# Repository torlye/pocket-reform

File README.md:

# MNT Pocket Reform: Swapped Ctrl and Hyper keys
This fork modifies `pocket-reform-keyboard-fw` to swap the position of the **Left Ctrl** and **Hyper** keys on the keyboard.

My muscle memory requires me to have the Ctrl key at the bottom left corner of the keyboard!

This fork also adds a few new key combinations:

| Shortcut | Function     |
|----------|--------------|
| HYPER+V  | Volume up    |
| HYPER+C  | Volume down  |
| HYPER+;  | Print screen |

## First-time setup
Run `./install-fw-dependencies.sh`

## Building and flashing
1. cd to `pocket-reform-keyboard-fw/pocket-hid`
2. Run `./build.sh` to build
3. Run the command `sudo sleep 5 && ./flash.sh`
4. Enter your sudo password (if necessary) to begin the sleep
5. Press Hyper+Enter and then x on the keyboard to enter firmware upload mode
6. Wait for flashing to complete and for the controller to reset

---

Original README follows:

---

# MNT Pocket Reform (Research Project)

This repository contains specifications, schematics, PCB and case designs, and firmware source code for the MNT Pocket Reform laptop.

## License

Copyright 2021 MNT Research GmbH.

The following licenses are used in the project, unless specified differently in a particular subfolder:

- Schematics, PCBs: [CERN-OHL-S v2](https://www.ohwr.org/project/cernohl/wikis/uploads/002d0b7d5066e6b3829168730237bddb/cern_ohl_s_v2.txt)
- Other documentation, artwork, photos and drawings that are not trademarks (see below): [CC-BY-SA 4.0](https://creativecommons.org/licenses/by-sa/4.0/legalcode)
- Software, firmware: Various. [GPL 3.0](https://www.gnu.org/licenses/gpl-3.0.en.html) if not specified otherwise in the file/subdirectory.

The "MNT" and "MNT REFORM" logos are trademarks of MNT Research GmbH. You may not use these in derived works. The reason for this is that we cannot be responsible for regulatory issues with derived boards and we cannot support them. If someone sees an MNT brand on a product, it has to be clear that it comes from MNT Research and not from a third party.

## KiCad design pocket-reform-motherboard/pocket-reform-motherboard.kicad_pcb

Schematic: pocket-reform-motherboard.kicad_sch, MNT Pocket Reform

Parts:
C1, C3, C13, C19, C20, C25, C27, C28, C29, C30, C31, C32, C33, C34, C35, C38, C40, C42, C43, C44, C45, C46, C48, C49, C50, C53, C54, C55, C57, C59, C60, C61, C62, C63, C64, C66, C68, C69, C70, C71, C72, C73, C74, C75, C76, C77, C78, C79, C80, C81, C84, C87, C95, C97, C99, C101, C104, C108, C109, C121, C127, C128, C130, C131, C132, C137, C138, C142, C143, C144, C145, C148, C151, C154, C155, C156: 0.1uF; C_0402_1005Metric; LCSC C307331
C2, C7, C12, C39, C47, C51, C56, C58, C65, C98, C105, C107, C112, C115, C129, C133, C136, C141, C152, C153, C157, C158: 10uF; C_0603_1608Metric; LCSC C194427
C4: 22uF; C_Elec_4x5.4; LCSC C3830031
C5: 47uF; CP_Elec_6.3x5.8; LCSC C688950
C6, C14, C15, C16, C17, C18, C116, C117, C118, C119, C120, C134: 22uF; C_0603_1608Metric; LCSC C86295
C8, C11, C82, C113, C114: 470nF; C_0603_1608Metric; LCSC C1623
C9, C10: 4.7uF; C_0603_1608Metric; LCSC C437419
C21, C23: 18pF; C_0402_1005Metric; LCSC C1549
C22, C24: 15pF; C_0402_1005Metric; LCSC C161530
C26, C36, C111, C125, C147: 1uF; C_0402_1005Metric; LCSC C52923
C37: 1nF; C_0402_1005Metric; LCSC C1523
C41, C146: 4.7uF; C_0402_1005Metric; LCSC C23733
C52: 10nF; C_0603_1608Metric; LCSC C1589
C67, C106: 22uF; C_0805_2012Metric; LCSC C45783
C83, C123, C124, C126: 47uF; C_0603_1608Metric; LCSC C140782
C85, C86, C88, C89, C90, C91, C92, C93: 0.22uF; C_0402_1005Metric; LCSC C1525
C94, C100: 10uF; C_0402_1005Metric; LCSC C315248
C96: DNP; C_0402_1005Metric; LCSC C1525; not fitted
C102, C103, C135: 47uF; C_1206_3216Metric; LCSC C94034
C110, C122: 10pF; C_0402_1005Metric; LCSC C32949
D1, D8, D9, D23: LED_RED; LED_0603_1608Metric; LCSC C965799
D2: ESDS314; SOT-23-5; LCSC C1847859
D3: MS2A40LWS; D_SOD-323; LCSC C7380001
D5: PMEG4050EP-FS; D_SOD-128; LCSC C42387310
D10: 19-337/R6GHBHC-A01/2T; LED_19-337_R6GHBHC-A01_2T; LCSC C264519
D12: SD0603S040S0R2; D_0603_1608Metric; LCSC C143772
FB2, FB9, FB10, FB12, FB13, FB14, FB15, FB16: 100@100MHz 3A; L_0603_1608Metric; LCSC C14709
FB5: DNP; L_0603_1608Metric; LCSC C14709; not fitted
GFX1: MountingHole; pocket-reform; LCSC DNP; not fitted
GFX2: MountingHole; pref-motherboard-badge; LCSC DNP; not fitted
H1, H2, H3, H4: MountingHole_Pad; MountingHole_2.2mm_M2_DIN965_Pad; LCSC DNP; not fitted
H5, H7: NGFF-Mount1; WA-SMSI-M2; LCSC C18198647
H8, H9: MountingHole_Pad; WA-SMSI-M2; LCSC C22431115
J1: CHARGER; JST_PH_S9B-PH-SM4-TB_1x09-1MP_P2.00mm_Horizontal; LCSC C278795
J2: DM3AT-SF-PEJM5; LCSC C114218
J3, J14: USB_C_Receptacle; MOLEX_105450-0101; LCSC C134092
J4: 09452812561; LCSC C19193264
J5: SYSCTL; JST_SH_SM04B-SRSS-TB_1x04-1MP_P1.00mm_Horizontal; LCSC C160404
J6: USB_INT1; JST_SH_SM04B-SRSS-TB_1x04-1MP_P1.00mm_Horizontal; LCSC C160404
J7: HDMI_D_1.4; HDMI-SMD_BX-HDMI-2-M19P; LCSC C18077696
J8: SIM_Card; MOLEX_78800-0001; LCSC C127364
J9: Conn_01x20; Hirose_FH12-20S-0.5SH_1x20-1MP_P0.50mm_Horizontal; LCSC C2906119
J10: 1-2199230-6; TE_1-2199230-6; LCSC C4710843
J11: Conn_01x33; Hirose_FH12-33S-0.5SH_1x33-1MP_P0.50mm_Horizontal; LCSC C19077727
J12: 2199230-5; TE_2199230-5; LCSC C4827729
J13: 3-2328724-1; TE_3-2328724-1; LCSC C52722586
J15: CONN_SPK; Molex_PicoBlade_53261-0271_1x02-1MP_P1.25mm_Horizontal; LCSC C177225
J16: SAMTEC_TSM-106-02-X-SH-A; LCSC C6290784
J17: POWSW; JST_SH_SM02B-SRSS-TB_1x02-1MP_P1.00mm_Horizontal; LCSC C160402
J18: CONN_HEAD; JST_SH_SM05B-SRSS-TB_1x05-1MP_P1.00mm_Horizontal; LCSC C136657
J20: QWIIC; JST_SH_SM04B-SRSS-TB_1x04-1MP_P1.00mm_Horizontal; LCSC C160404
L1: 12uH; L_Taiyo-Yuden_NR-30xx; LCSC C167758
L2: 3.3uH; L_1210_3225Metric; LCSC C337905
L3: 3.3uH; L_Coilcraft_XAL6060-XXX; LCSC C3040366
L4: 2.2uH; L_Coilcraft_XAL6060-XXX; LCSC C167218
L5, L6: 15uH; L_Taiyo-Yuden_NR-30xx; LCSC C668450
R1, R16, R29, R34, R35, R36, R45, R58, R60, R61, R63, R71, R110, R165: 1k; R_0402_1005Metric; LCSC C11702
R2: 1M; R_0402_1005Metric; LCSC C26083
R3: 90.9K 1%; R_0402_1005Metric; LCSC C26989
R4, R5, R11, R12, R13, R19, R27, R46, R50, R53, R54, R62, R65, R66, R67, R81, R104, R105, R106, R107, R108, R109, R116, R118, R122, R123, R124, R133, R136, R139, R148, R149, R151, R152, R153, R154, R155, R164, R166, R167, R168, R169, R170: 0; R_0402_1005Metric; LCSC C17168
R6: 470k; R_0402_1005Metric; LCSC C25790
R7: 124k; R_0402_1005Metric; LCSC C36777
R10, R20, R22, R24, R26, R28, R30, R38, R44, R49, R52, R56, R68, R72, R75, R85, R94, R96, R111, R113, R114, R115, R117, R119, R121, R125, R127, R128, R130, R131, R134, R135, R138, R141, R142, R143, R144, R145, R156, R159, R160, R162, R163: 10k; R_0402_1005Metric; LCSC C25744
R14: 8.25k; R_0402_1005Metric; LCSC C95598
R15: 33k; R_0402_1005Metric; LCSC C25779
R17, R51, R69, R70, R87, R91, R112, R150, R157: 100k; R_0402_1005Metric; LCSC C25741
R18: 24.9k; R_0402_1005Metric; LCSC C25874
R21, R74, R78, R88: DNP; R_0402_1005Metric; LCSC DNP; not fitted
R23: 9.53K 1%; R_0402_1005Metric; LCSC C96273
R25, R42, R43, R57, R59, R95, R101, R120, R161: 4.7k; R_0402_1005Metric; LCSC C25900
R31: 0; R_0603_1608Metric; LCSC C21189
R32, R33, R64, R89, R93, R132, R137, R158: 2.2k; R_0402_1005Metric; LCSC C25879
R37, R39, R40, R41: 75 1%; R_0402_1005Metric; LCSC C25133
R47, R48: 27.4; R_0402_1005Metric; LCSC C31439
R55, R76, R77, R79, R80, R82, R86: 33; R_0402_1005Metric; LCSC C25105
R73, R97, R98, R99, R100: 47k; R_0402_1005Metric; LCSC C25792
R83, R84: 22k; R_0402_1005Metric; LCSC C25768
R90: 27k; R_0402_1005Metric; LCSC C25771
R92, R126: 4.99k; R_0402_1005Metric; LCSC C25903
R102: 43.2k; R_0402_1005Metric; LCSC C25894
R103: 0; R_0402_1005Metric; LCSC C17168; not fitted
R129: 6.8k; R_0402_1005Metric; LCSC C25917
R198, R199: 49.9; R_0402_1005Metric; LCSC C25120
SW1: SW_DIP_x01; SW_DIP_SPSTx01_Slide_Copal_CHS-01A_W5.08mm_P1.27mm_JPin; LCSC C3312106
SW2, SW3: RESET; SW_Push_1P1T_NO_CK_KMR2; LCSC C318893
TP1, TP2, TP3, TP4, TP5, TP6, TP10, TP11, TP12, TP13, TP14, TP15, TP16, TP17, TP18, TP19, TP20, TP21: TestPoint; TestPoint_Pad_D1.0mm; not fitted
TP7: UUART_SUSPEND; TestPoint_Pad_D1.0mm; not fitted
TP8: UUART_WAKEUP; TestPoint_Pad_D1.0mm; not fitted
TP9: UUART_nPOWER; TestPoint_Pad_D1.0mm; not fitted
TR1: TG111-MSC13LF; Transformer_Ethernet_HALO_TG111-MSC13; LCSC C501477
U1: reform2-som-connector; TE_1473149-4; LCSC C590722
U2, U30, U31, U37: TS3USB30EDGSR; VSSOP-10_3x3mm_P0.5mm; LCSC C131998
U3: LM2830XQMFE/NOPB; SOT-23-5; LCSC C2072452
U4: TLV75718PDBV; SOT-23-5; LCSC C507270
U5: LM73100RPWR; IC_LM73100RPWR; PARTREV 08/2019; LCSC C3210761
U6, U28: LM62460; CONV_LM61495QRPHRQ1; LCSC C3198091
U7: 74LVC1G34; SOT-353_SC-70-5; LCSC C353880
U8: RP2040; RP2040-QFN-56; LCSC C2040
U9: TPS7A0533PDBZ; SOT-23; LCSC C2877921
U10: W25Q32JVSS; SOIC-8_5.3x5.3mm_P1.27mm; LCSC C179173
U11: PCF8523T; SOIC-8_3.9x4.9mm_P1.27mm; LCSC C2651516
U12, U29, U32, U36, U40, U41: AP22615AWU-7; SOT-23-6; LCSC C2680357
U13, U24: TXS0108EPW; TSSOP-20_4.4x6.5mm_P0.65mm; LCSC C17206
U14: SN74AVC1T45; SOT-23-6; LCSC C131978
U15, U16, U19, U20, U21, U22: TPD4E02B04DQA; USON-10_2.5x1.0mm_P0.5mm; LCSC C2841426
U17: TPD12S521; TSSOP50P640X120-38N; LCSC C126920
U18: TLV320AIC3100; VQFN-32-1EP_5x5mm_P0.5mm_EP3.5x3.5mm; LCSC C478458
U23: FUSB302BMPX; WQFN-14-1EP_2.5x2.5mm_P0.5mm_EP1.45x1.45mm; LCSC C132291
U25: TUSB8041; QFN-64-1EP_9x9mm_P0.5mm_EP6x6mm_ThermalVias; LCSC C544686
U27: TVS2200DRV; WSON-6-1EP_2x2mm_P0.65mm_EP1x1.6mm; LCSC C523793
U33: AT24CS02-STUM; SOT-23-5; LCSC C2060969
U34: PCA9536DP; TSSOP-8_3x3mm_P0.65mm; LCSC C14674
U35: TMUXHS4446RETR; IC_TMUXHS4446RETR; PARTREV FEBRUARY 2024; LCSC C35471229
U38: CY7C65215-32LTXI; QFN-32-1EP_5x5mm_P0.5mm_EP3.45x3.45mm; LCSC C22451897
U39: PCA9557PW; TSSOP-16_4.4x5mm_P0.65mm; LCSC C141380
U42: TPS560430X3FDBVR; SOT-23-6; LCSC C2071721
Y1: 24MHz; Crystal_SMD_Abracon_ABM8G-4Pin_3.2x2.5mm; LCSC C91744
Y2: 12MHz 12pF; Crystal_SMD_3225-4Pin_3.2x2.5mm; LCSC C20625731
Y3: 32.768 kHz; Crystal_SMD_3215-2Pin_3.2x1.5mm; LCSC C48615

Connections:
3V3_ENABLE_L: R71.2, R121.2, U32.4 (EN), U39.9 (IO2)
5V_ENABLE_L: R63.2, U39.7 (IO1)
+1V1: C134.1, L2.2, R14.1, R50.1, TP15.1 (1_1)
+1V8: C10.1, C20.1, C41.1, FB12.1, J13.1, R53.1, R81.2, TP14.1 (1_1), U4.5 (OUT), U7.5 (VCC)
+3V3: C58.1, C77.1, C116.1, C117.1, C118.1, C119.1, C120.1, C133.1, C141.1, FB5.2, FB13.2, L4.2, R4.2, R24.1, R26.1, R29.1, R30.1, R34.1, R42.2, R43.2, R54.2, R85.1, R87.1, R90.1, R91.1, R92.1, R97.2, R98.2, R99.2, R100.2, R112.2, R128.2, R136.2, R154.2, R156.2, R157.1, R160.2, R164.2, TP13.1 (1_1), U28.5 (BIAS), U29.6 (IN), U36.6 (IN), U40.6 (IN)
+5V: C14.1, C15.1, C16.1, C17.1, C18.1, C39.1, C47.1, C73.2, C108.1, C136.1, D12.2 (A), FB2.1, L3.2, R3.1, R11.1, R17.1, R51.2, R62.1, R68.2, R103.2, R126.1, R142.2, TP12.1 (1_1), U1.1 (5V), U1.2 (5V), U1.3 (5V), U1.4 (5V), U1.5 (5V), U1.6 (5V), U6.5 (BIAS), U9.3 (VI), U12.6 (IN), U17.1 (5V_SUPPLY), U41.6 (IN)
/3V3_1V8: C9.1, R4.1, U4.1 (IN), U4.3 (EN)
/AUD_3V3: C50.1, C51.1, C97.1, C107.1, FB5.1, J18.1, U9.2 (VO), U18.17 (AVDD), U18.28 (HPVDD)
/DP0_N: J9.8, R148.1
/DP0_P: J9.7, R149.1
/DP1_N: J9.5, R151.1
/DP1_P: J9.4, R152.1
/DP2_N: J9.2, R169.1
/DP2_P: J9.1, R170.1
/DP3_N: J9.11, R167.1
/DP3_P: J9.10, R168.1
/DP_AUX_N: C138.2, J9.15
/DP_AUX_P: C137.2, J9.16
/M2_SMB_ALERTn: J10.44
/M2_SMB_CLK: J10.40
/M2_SMB_DATA: J10.42
/MODEM_3V3: C52.1, C53.1, C54.1, C55.1, C83.1, C123.1, J12.2, J12.4, J12.70, J12.72, J12.74, R1.1, R164.1, R166.2
/M_ANTCTL0: J12.59
/M_ANTCTL1: J12.61
/M_ANTCTL2: J12.58
/M_ANTCTL3: J12.56
/M_COEX1: J12.64
/M_COEX2: J12.62
/M_CONFIG_0: J12.21
/M_CONFIG_1: J12.69
/M_CONFIG_2: J12.75
/M_CONFIG_3: J12.1
/M_I2C_SCL: J12.38
/M_I2C_SDA: J12.68
/M_I2S_MCLK(IO): J12.60
/M_LAA_TX_EN: J12.63
/M_SIM1_DET: J12.66
/M_SIM2_CLK: J12.44
/M_SIM2_DATA: J12.42
/M_SIM2_DET: J12.40
/M_SIM2_PWR: J12.48
/M_SIM2_RESET: J12.46
/M_VIO_1V8: J12.65
/PCIE_3V3: C59.1, C60.1, C61.1, C124.1, C126.1, J10.2, J10.4, J10.12, J10.14, J10.16, J10.18, J10.70, J10.72, J10.74, R110.1, U29.1 (OUT)
/RRUD+: R47.1, U8.47 (USB_DP)
/RRUD-: R48.1, U8.46 (USB_DM)
/RUD+: R47.2, U2.3 (D2+), U30.4 (D+)
/RUD-: R48.2, U2.7 (D2-), U30.6 (D-)
/SYSLED_B: R61.1, U8.18 (GPIO15)
/SYSLED_G: R58.1, U8.28 (GPIO17)
/SYSLED_R: R60.1, U8.27 (GPIO16)
/USB1_C_RXN: C128.2, U25.56 (USB_SSTXM_UP)
/USB1_C_RXP: C127.2, U25.55 (USB_SSTXP_UP)
/USBH_1A_AC_TXN: C85.1, J3.A3 (TX1-), U20.4 (IO3), U20.7 (IO3)
/USBH_1A_AC_TXP: C88.1, J3.A2 (TX1+), U20.5 (IO4), U20.6 (IO4)
/USBH_1B_AC_TXN: C86.1, J3.B3 (TX2-), U22.1 (IO1), U22.10 (IO1)
/USBH_1B_AC_TXP: C89.1, J3.B2 (TX2+), U22.2 (IO2), U22.9 (IO2)
/USBM1_AC_RXN: J14.B10 (RX1-), U19.1 (IO1), U19.10 (IO1), U35.25 (CRX1+)
/USBM1_AC_RXP: J14.B11 (RX1+), U19.2 (IO2), U19.9 (IO2), U35.24 (CRX1-)
/USBM1_AC_TXN: C90.2, J14.A3 (TX1-), U19.4 (IO3), U19.7 (IO3)
/USBM1_AC_TXP: C92.2, J14.A2 (TX1+), U19.5 (IO4), U19.6 (IO4)
/USBM1_TXN: C92.1, U35.27 (CTX1-)
/USBM1_TXP: C90.1, U35.28 (CTX1+)
/USBM2_AC_RXN: J14.A10 (RX2-), U21.1 (IO1), U21.10 (IO1), U35.34 (CRX2+)
/USBM2_AC_RXP: J14.A11 (RX2+), U21.2 (IO2), U21.9 (IO2), U35.33 (CRX2-)
/USBM2_AC_TXN: C91.2, J14.B3 (TX2-), U21.4 (IO3), U21.7 (IO3)
/USBM2_AC_TXP: C93.2, J14.B2 (TX2+), U21.5 (IO4), U21.6 (IO4)
/USBM2_TXN: C93.1, U35.30 (CTX2-)
/USBM2_TXP: C91.1, U35.31 (CTX2+)
/USBM_SBU1: J14.A8 (SBU1), U35.22 (SBU1)
/USBM_SBU2: J14.B8 (SBU2), U35.21 (SBU2)
/USB_UART_3V3: C146.1, R134.1, R135.1, R136.1, U38.1 (VDDD), U38.19 (VBUS), U38.23 (VDDD)
/VCONN: R166.1, U23.12 (VCONN), U23.13 (VCONN)
/VIN_FOR_3V3: C112.1, C113.1, C114.1, C115.1, U28.2 (VIN2), U28.14 (VIN1), U32.1 (OUT)
/XUD+: U2.4 (D+), U31.3 (D2+)
/XUD-: U2.6 (D-), U31.7 (D2-)
/~M_LED1: D1.1 (K), J12.10
/~M_W_DISABLE1: J12.8, R65.1
/~M_W_DISABLE2: J12.26, R66.1
/~PCIE2_CLKREQ: J12.52
/~PCIE2_WAKE: J12.54
CHG_VCC: C4.1, J1.1, J1.2, R6.1, U5.5 (IN)
DAC_BCLK: R76.1, U1.170 (SAI2_TXC)
DAC_DIN: R79.1, U1.166 (SAI2_RXD)
DAC_DOUT: R77.1, U1.178 (SAI2_TXD)
DAC_MCLK: R82.2, U1.176 (SAI2_MCLK)
DAC_SCL: R42.1, U1.101 (I2C3_SCL), U11.6 (SCL), U18.10 (SCL)
DAC_SDA: R43.1, U1.103 (I2C3_SDA), U11.5 (SDA), U18.9 (SDA)
DAC_TXFS: R80.1, U1.172 (SAI2_TXFS)
DISP_1BL_2EN: J13.26, U1.105 (GPIO1_IO10)
DISP_1EN_2BL: J13.2, R46.2, R138.1, R139.2
DISP_2_PWM: R139.1, U8.9 (GPIO7)
DISP_BACKLIGHT_3V3: C105.1, J13.5, J13.6, J13.28, J13.29, J13.30, J13.31, R138.2, U36.1 (OUT)
DISP_BL_PWR_EN_L: R130.2, U36.4 (EN), U39.12 (IO5)
DP_HPD: J9.17, R165.2
DSI_CLK_N: J11.19, J13.17
DSI_CLK_P: J11.20, J13.16
DSI_D0_N: J11.25, J13.20
DSI_D0_P: J11.26, J13.19
DSI_D1_N: J11.22, J13.14
DSI_D1_P: J11.23, J13.13
DSI_D2_N: J11.16, J13.11
DSI_D2_P: J11.17, J13.10
DSI_D3_N: J11.13, J13.23
DSI_D3_P: J11.14, J13.22
ETH0_A+: TR1.2 (TD1+), U1.29 (TRX0_P)
ETH0_A-: TR1.3 (TD1-), U1.27 (TRX0_N)
ETH0_B+: TR1.5 (TD2+), U1.23 (TRX1_P)
ETH0_B-: TR1.6 (TD2-), U1.21 (TRX1_N)
ETH0_C+: TR1.8 (TD3+), U1.17 (TRX2_P)
ETH0_C-: TR1.9 (TD3-), U1.15 (TRX2_N)
ETH0_D+: TR1.11 (TD4+), U1.11 (TRX3_P)
ETH0_D-: TR1.12 (TD4-), U1.9 (TRX3_N)
ETH0_DA+: J4.1, TR1.23 (MTX1+)
ETH0_DA-: J4.2, TR1.22 (MTX1-)
ETH0_DB+: J4.6, TR1.20 (MTX2+)
ETH0_DB-: J4.7, TR1.19 (MTX2-)
ETH0_DC+: J4.4, TR1.17 (MTX3+)
ETH0_DC-: J4.5, TR1.16 (MTX3-)
ETH0_DD+: J4.9, TR1.14 (MX4+)
ETH0_DD-: J4.10, TR1.13 (MX4-)
ETH0_LED_LINK1: D9.1 (K), U1.83 (JTAG_TDO)
ETH0_LED_RX: D8.1 (K), U1.79 (JTAG_MOD)
GND: C1.2, C2.2, C3.2, C4.2, C5.2, C6.2, C7.2, C8.2, C9.2, C10.2, C11.2, C12.2, C13.1, C14.2, C15.2, C16.2, C17.2, C18.2, C20.2, C21.2, C22.2, C23.2, C24.2, C25.2, C26.2, C27.2, C28.2, C29.2, C30.2, C31.2, C32.2, C33.2, C34.2, C35.2, C36.2, C37.2, C38.2, C39.2, C40.2, C41.2, C42.2, C43.2, C44.2, C45.2, C46.1, C47.2, C48.2, C49.2, C52.2, C53.2, C54.2, C55.2, C56.2, C58.2, C59.2, C60.2, C61.2, C62.2, C63.2, C64.2, C65.2, C66.2, C68.2, C69.2, C70.2, C71.2, C72.1, C73.1, C74.2, C75.2, C77.2, C79.2, C80.2, C81.2, C83.2, C84.2, C87.2, C94.2, C95.1, C98.2, C100.2, C101.2, C105.2, C108.2, C111.1, C112.2, C113.2, C114.2, C115.2, C116.2, C117.2, C118.2, C119.2, C120.2, C123.2, C124.2, C125.1, C126.2, C129.2, C130.2, C131.2, C132.1, C133.2, C134.2, C135.2, C136.2, C141.2, C142.2, C143.2, C144.2, C145.2, C146.2, C147.2, C148.2, C151.2, C152.2, C153.2, C154.1, C155.1, C156.1, C157.2, C158.2, D2.2 (A), D3.2 (A), D10.1 (RK), D10.2 (GK), D10.3 (BK), FB14.1, FB15.1, FB16.1, H1.1 (1_1), H2.1 (1_1), H3.1 (1_1), H4.1 (1_1), H5.1 (1_1), H7.1 (1_1), H8.1 (1_1), H9.1 (1_1), J1.8, J1.9, J2.6 (VSS), J2.P1 (SHIELD), J2.P2 (SHIELD), J2.P3 (SHIELD), J2.P4 (SHIELD), J2.SWA (DET_A), J3.A1 (GND), J3.A12 (GND), J3.B1 (GND), J3.B12 (GND), J3.S1 (SHIELD), J4.3, J4.8, J4.SH, J5.4, J6.4, J7.4 (D2S), J7.7 (D1S), J7.10 (D0S), J7.13 (CKS), J7.16 (GND), J7.20 (SH), J8.5 (GND), J8.P1 (SHIELD), J8.P2 (SHIELD), J8.P3 (SHIELD), J8.P4 (SHIELD), J9.3, J9.6, J9.9, J9.12, J9.13, J10.1, J10.3, J10.9, J10.15, J10.21, J10.27, J10.33, J10.39, J10.45, J10.51, J10.57, J10.71, J10.73, J10.75, J10.S1 (SHIELD), J10.S2 (SHIELD), J11.1, J11.2, J11.12, J11.15, J11.18, J11.21, J11.24, J11.27, J11.30, J12.3, J12.5, J12.11, J12.27, J12.33, J12.39, J12.45, J12.51, J12.57, J12.71, J12.73, J12.SH1 (SHIELD), J12.SH2 (SHIELD), J13.3, J13.4, J13.9, J13.12, J13.15, J13.18, J13.21, J13.24, J13.27, J13.S1 (Pin_32), J13.S2 (Pin_33), J14.A1 (GND), J14.A12 (GND), J14.B1 (GND), J14.B12 (GND), J14.S1 (SHIELD), J16.1, J16.4, J17.1, J20.1, R10.2, R15.2, R16.2, R18.2, R20.2, R22.2, R23.1, R32.2, R33.2, R49.1, R69.2, R73.2, R94.2, R95.1, R96.2, R101.1, R102.2, R104.2, R105.2, R106.2, R107.2, R108.2, R109.2, R115.2, R120.2, R121.1, R125.2, R129.2, R130.1, R141.2, R143.1, R144.1, R145.1, R150.2, R158.2, R159.1, R161.2, R162.1, R198.1, R199.1, SW1.2, SW2.2 (B), SW3.2 (B), TP3.1 (1_1), TP19.1 (1_1), U1.7 (GND), U1.13 (GND), U1.19 (GND), U1.25 (GND), U1.31 (GND), U1.41 (GND), U1.44 (GND), U1.47 (GND), U1.50 (GND), U1.53 (GND), U1.56 (GND), U1.59 (GND), U1.62 (GND), U1.65 (GND), U1.68 (GND), U1.71 (GND), U1.74 (GND), U1.80 (GND), U1.94 (GND), U1.95 (GND), U1.98 (GND), U1.99 (GND), U1.104 (GND), U1.110 (GND), U1.111 (GND), U1.116 (GND), U1.117 (GND), U1.123 (GND), U1.129 (GND), U1.161 (GND), U1.167 (GND), U1.173 (GND), U1.179 (GND), U1.185 (GND), U1.191 (GND), U2.5 (GND), U3.2 (GND), U4.2 (GND), U5.8 (GND), U6.1 (PGND2), U6.8 (AGND), U6.12 (SYNC/MODE), U6.15 (PGND1), U7.3 (GND), U8.19 (TESTEN), U8.57 (GND), U9.1 (GND), U10.4 (GND), U11.4 (VSS), U12.2 (GND), U13.11 (GND), U14.2 (GND), U15.3 (G), U15.8 (G), U16.3 (G), U16.8 (G), U17.3 (GND), U17.5 (TMDS_GND), U17.8 (TMDS_GND), U17.11 (TMDS_GND), U17.14 (TMDS_GND), U17.25 (TMDS_GND), U17.28 (TMDS_GND), U17.31 (TMDS_GND), U17.34 (TMDS_GND), U17.36 (GND), U18.1 (IOVSS), U18.18 (DVSS), U19.3 (G), U19.8 (G), U20.3 (G), U20.8 (G), U21.3 (G), U21.8 (G), U22.3 (G), U22.8 (G), U23.8 (GND), U23.9 (GND), U23.15 (GND), U24.11 (GND), U25.65 (VSS), U27.1 (GND), U27.2 (GND), U27.3 (GND), U27.7 (GND), U28.1 (PGND2), U28.8 (AGND), U28.12 (SYNC/MODE), U28.15 (PGND1), U29.2 (GND), U30.5 (GND), U31.5 (GND), U32.2 (GND), U33.2 (GND), U33.5 (WP), U34.4 (VSS), U35.15 (GND), U35.18 (GND), U35.37 (GND), U35.41 (GND), U36.2 (GND), U37.5 (GND), U38.4 (VSSD), U38.17 (VSSD), U38.20 (VSSD), U38.24 (VSSA), U39.4 (A1), U39.5 (A2), U39.8 (VSS), U40.2 (GND), U41.2 (GND), U42.2 (GND), Y1.2, Y1.4, Y2.2, Y2.4
GNDA: C50.2, C51.2, C57.2, C67.2, C76.2, C78.2, C96.1, C97.2, C99.2, C106.2, C107.2, FB14.2, FB15.2, FB16.2, J18.5, U18.16 (AVSS), U18.20 (SPKVSS), U18.25 (SPKVSS), U18.29 (HPVSS), U18.33 (EP)
HDMI_AUXN: U1.189 (HDMI_AUX_N)
HDMI_AUXP: U1.187 (HDMI_AUX_P)
HDMI_CEC: R100.1, U1.197 (HDMI_CEC), U17.16 (CE_REMOTE_IN)
HDMI_CLKN: J7.14 (CK-), U1.163 (HDMI_CLK_N), U17.15 (TMDS_CK-), U17.24 (TMDS_CK-)
HDMI_CLKP: J7.12 (CK+), U1.165 (HDMI_CLK_P), U17.13 (TMDS_CK+), U17.26 (TMDS_CK+)
HDMI_HPD: R97.1, U1.199 (HDMI_HPD), U17.19 (HOTPLUG_DET_IN)
HDMI_SCL: R98.1, U1.195 (HDMI_DDC_SCL), U17.17 (DDC_CLK_IN)
HDMI_SDA: R99.1, U1.193 (HDMI_DDC_SDA), U17.18 (DDC_DAT_IN)
HDMI_TX0N: J7.11 (D0-), U1.169 (HDMI_TX0_N), U17.12 (TMDS_D0-), U17.27 (TMDS_D0-)
HDMI_TX0P: J7.9 (D0+), U1.171 (HDMI_TX0_P), U17.10 (TMDS_D0+), U17.29 (TMDS_D0+)
HDMI_TX1N: J7.8 (D1-), U1.175 (HDMI_TX1_N), U17.9 (TMDS_D1-), U17.30 (TMDS_D1-)
HDMI_TX1P: J7.6 (D1+), U1.177 (HDMI_TX1_P), U17.7 (TMDS_D1+), U17.32 (TMDS_D1+)
HDMI_TX2N: J7.5 (D2-), U1.181 (HDMI_TX2_N), U17.6 (TMDS_D2-), U17.33 (TMDS_D2-)
HDMI_TX2P: J7.3 (D2+), U1.183 (HDMI_TX2_P), U17.4 (TMDS_D2+), U17.35 (TMDS_D2+)
HEAD_HPL: C103.2, J18.3
HEAD_HPR: C102.2, J18.4
HEAD_MIC: C96.2, C104.2, J18.2, R64.1, U18.11 (VOL/MICDET)
HUB_PWR_EN_L: R162.2, U39.10 (IO3), U40.4 (EN)
IMX_RESETn: R30.2, U1.87 (EXT_RESET_N)
IMX_RTC_IRQ: R67.1, U1.141 (RTC_IRQ)
IMX_UART1_RX: J16.5, R26.2, R134.2, U1.126 (UART1_RXD), U38.30 (SCB0_4/GPIO_5)
IMX_UART1_TX: J16.6, U1.128 (UART1_TXD), U38.2 (SCB0_0/GPIO_8)
IMX_UART2_RX: J16.2, R24.2, R135.2, U1.122 (UART2_RXD), U38.6 (SCB1_1/GPIO_11)
IMX_UART2_TX: J16.3, U1.124 (UART2_TXD), U38.5 (SCB1_0/GPIO_10)
IMX_WAKE: U1.145 (GPIO1_IO3), U8.30 (GPIO19)
KICKSTART: R44.2, R45.2, SW3.1 (A)
LPC_MISO: TP11.1 (1_1), U1.93 (ECSPI2_MISO), U8.14 (GPIO11)
LPC_MOSI: TP5.1 (1_1), U1.91 (ECSPI2_MOSI), U8.11 (GPIO8)
LPC_SCK: TP10.1 (1_1), U1.97 (ECSPI2_SCLK), U8.13 (GPIO10)
LPC_SS0: TP6.1 (1_1), U1.89 (ECSPI2_SS0), U8.12 (GPIO9)
MODEM_PWROFFn: J12.6, U8.29 (GPIO18)
MODEM_RESET: J12.67, U24.6 (A5)
MODEM_RESET_3V3: U8.31 (GPIO20), U24.15 (B5)
unnamed: C24.1, R35.1, Y2.3
unnamed: C37.1, R37.2, R39.2, R40.2, R41.2
unnamed: C57.1, C67.1, C99.1, C106.1, FB2.2, U18.21 (SPKVDD), U18.24 (SPKVDD)
unnamed: C110.2, R126.2
unnamed: C122.2, R92.2
unnamed: D1.2 (A), R1.2
unnamed: D3.1 (K), L2.1, U3.1 (SW)
unnamed: D8.2 (A), R29.2
unnamed: D9.2 (A), R34.2
unnamed: D10.4 (BA), R61.2
unnamed: D10.5 (GA), R60.2
unnamed: D10.6 (RA), R58.2
unnamed: D12.1 (K), R89.1, R93.1
unnamed: D23.2 (A), R110.2
unnamed: D23.1 (K), J10.10
unnamed: FB9.1, U18.22 (SPKP), U18.26 (SPKP)
unnamed: FB9.2, L5.1
unnamed: FB10.1, U18.19 (SPKM), U18.23 (SPKM)
unnamed: FB10.2, L6.1
unnamed: J2.5 (CLK), U14.4 (B)
unnamed: C63.1, C64.1, C65.1, C66.1, J2.4 (VDD), R154.1, U13.19 (VCCB), U14.6 (VCCB)
unnamed: J3.A5 (CC1), R83.1, U16.1 (IO1), U16.10 (IO1)
unnamed: J3.B5 (CC2), R84.1, U16.2 (IO2), U16.9 (IO2)
unnamed: J6.1, R62.2
unnamed: C87.1, J7.19 (+5V), U17.38 (5V_OUT)
unnamed: J7.15 (CEC), R90.2, U17.23 (CE_REMOTE_OUT)
unnamed: J7.1 (HPD/HEAC-), R96.1, U17.20 (HOTPLUG_DET_OUT)
unnamed: J7.17 (SCL), R89.2, U17.22 (DDC_CLK_OUT)
unnamed: J7.18 (SDA), R93.2, U17.21 (DDC_DAT_OUT)
unnamed: J9.18, J9.19, J9.20, R103.1
unnamed: J10.11, R107.1
unnamed: J10.13, R104.1
unnamed: J10.23, R108.1
unnamed: J10.25, R105.1
unnamed: J10.35, R109.1
unnamed: J10.37, R106.1
unnamed: J14.A5 (CC1), TP20.1 (1_1), U15.1 (IO1), U15.10 (IO1), U23.10 (CC1), U23.11 (CC1)
unnamed: J14.B5 (CC2), TP21.1 (1_1), U15.2 (IO2), U15.9 (IO2), U23.1 (CC2), U23.14 (CC2)
unnamed: C76.1, C82.1, J15.1, L5.2
unnamed: C78.1, C82.2, J15.2, L6.2
unnamed: R40.1, TR1.21 (MCT2)
unnamed: R39.1, TR1.18 (MCT3)
unnamed: R37.1, TR1.15 (MCT4)
unnamed: R41.1, TR1.24 (MTC1)
unnamed: C42.1, TR1.1 (TCT1)
unnamed: C43.1, TR1.4 (TCT2)
unnamed: C44.1, TR1.7 (TCT3)
unnamed: C45.1, TR1.10 (TCT4)
unnamed: R116.1, U1.139 (FAST_BOOT)
unnamed: R74.2, U1.180 (SAI3_MCLK/PWM4)
unnamed: R88.2, U1.200 (SAI3_RXC)
unnamed: R21.2, U1.198 (SAI3_RXFS)
unnamed: R86.2, U1.192 (SAI3_TXC)
unnamed: R55.2, U1.190 (SAI3_TXFS)
unnamed: R78.2, U1.164 (SPDIF_RX/PWM2)
unnamed: R13.1, U1.32 (UART3_RXD)
unnamed: R12.2, U1.30 (UART3_TXD)
unnamed: R153.1, U1.137 (UART4_RXD)
unnamed: R11.2, U1.118 (USB1_VBUS)
unnamed: R163.2, U3.4 (EN)
unnamed: R10.1, R14.2, U3.3 (FB)
unnamed: R27.2, R163.1, U3.5 (Vin)
unnamed: R6.2, R7.1, U5.1 (EN/UVLO)
unnamed: R16.1, U5.9 (IMON)
unnamed: R7.2, R15.1, U5.2 (OVLO)
unnamed: C19.1, U6.3 (RBOOT), U6.4 (CBOOT)
unnamed: R63.1, R125.1, U6.13 (EN)
unnamed: C110.1, R17.2, R18.1, U6.7 (FB)
unnamed: R51.1, U6.10 (RESET)
unnamed: C111.2, U6.6 (VCC), U6.9 (RT), U6.11 (SPSP)
unnamed: C19.2, L3.1, U6.16 (SW)
unnamed: R165.1, U8.36 (GPIO24)
unnamed: R45.1, U8.37 (GPIO25)
unnamed: C26.1, C28.1, C29.1, C151.1, U8.23 (DVDD), U8.45 (VREG_VOUT), U8.50 (DVDD)
unnamed: C22.1, U8.20 (XIN), Y2.1
unnamed: R35.2, U8.21 (XOUT)
unnamed: U11.1 (OSCI), Y3.1
unnamed: U11.2 (OSCO), Y3.2
unnamed: R19.1, U11.3 (VBAT)
unnamed: R67.2, U11.7 (~INT1/CLKOUT)
unnamed: R68.1, U12.3 (FLG)
unnamed: R32.1, U12.5 (ISET)
unnamed: R75.2, U13.10 (OE), U14.5 (DIR)
unnamed: C48.1, C49.1, R75.1, R81.1, U13.2 (VCCA), U14.1 (VCCA)
unnamed: C72.2, U17.37 (ESD_BYP)
unnamed: R85.2, U17.2 (LV_SUPPLY)
unnamed: R76.2, U18.7 (BCLK)
unnamed: R77.2, U18.5 (DIN)
unnamed: R79.2, U18.4 (DOUT)
unnamed: C56.1, C62.1, FB12.2, R70.2, U18.3 (DVDD)
unnamed: C103.1, U18.27 (HPL)
unnamed: C102.1, U18.30 (HPR)
unnamed: C95.2, C98.1, FB13.1, U18.2 (IOVDD)
unnamed: R82.1, U18.8 (MCLK)
unnamed: C104.1, U18.14 (MIC1RP)
unnamed: R64.2, U18.12 (MICBIAS)
unnamed: R80.2, U18.6 (WCLK)
unnamed: R70.1, U18.31 (~RESET)
unnamed: R52.2, U24.10 (OE)
unnamed: C68.1, R28.1, R52.1, R53.2, U24.2 (VCCA)
unnamed: C69.1, R54.1, U24.19 (VCCB)
unnamed: R25.1, U25.40 (FULLPWRMGMTz/SMBA1/SS_UP)
unnamed: R101.2, U25.42 (GANGED/SMBA2/HS_UP)
unnamed: R5.1, U25.50 (GRSTz)
unnamed: R95.2, U25.49 (TEST)
unnamed: R23.2, U25.64 (USB_R1)
unnamed: R3.2, R22.1, U25.48 (USB_VBUS)
unnamed: C23.1, R2.2, U25.62 (XI), Y1.3
unnamed: C21.1, R2.1, U25.61 (XO), Y1.1
unnamed: C121.1, U28.3 (RBOOT), U28.4 (CBOOT)
unnamed: R71.1, R94.1, U28.13 (EN)
unnamed: C122.1, R91.2, R102.1, U28.7 (FB)
unnamed: R112.1, U28.10 (RESET)
unnamed: C125.2, U28.6 (VCC), U28.9 (RT), U28.11 (SPSP)
unnamed: C121.2, L4.1, U28.16 (SW)
unnamed: R156.1, U29.3 (FLG)
unnamed: R158.1, U29.5 (ISET)
unnamed: R119.1, U32.3 (FLG)
unnamed: R120.1, U32.5 (ISET)
unnamed: R122.1, U34.1 (IO0)
unnamed: R123.1, U34.2 (IO1)
unnamed: R124.1, U34.3 (IO2)
unnamed: R115.1, R118.1, U34.5 (IO3)
unnamed: R144.2, U35.14 (A0)
unnamed: R145.2, U35.35 (CONF0/A1)
unnamed: R111.1, U35.1 (MODE0)
unnamed: R127.1, U35.13 (MODE1)
unnamed: R128.1, U36.3 (FLG)
unnamed: R129.1, U36.5 (ISET)
unnamed: C145.1, R133.2, U37.10 (VCC)
unnamed: TP9.1 (1_1), U38.31 (GPIO_6)
unnamed: TP7.1 (1_1), U38.11 (SUSPEND)
unnamed: C147.1, U38.16 (VCCD)
unnamed: TP8.1 (1_1), U38.12 (WAKEUP)
unnamed: R132.2, U39.3 (A0)
unnamed: R46.1, U39.6 (IO0)
unnamed: R155.2, U39.14 (IO7)
unnamed: R137.2, U39.15 (~RESET)
unnamed: R160.1, U40.3 (FLG)
unnamed: R161.1, U40.5 (ISET)
unnamed: R142.1, U41.3 (FLG)
unnamed: R33.1, U41.5 (ISET)
unnamed: C109.2, U42.1 (CB)
unnamed: C109.1, L1.1, U42.6 (SW)
PCIE1_CLKREQn: J10.52, R153.2
PCIE1_CLK_N: J10.53, R199.2, U1.60 (PCIE1_REFCLK_N)
PCIE1_CLK_P: J10.55, R198.2, U1.58 (PCIE1_REFCLK_P)
PCIE1_RESETn: J10.50, U1.37 (PCIE_RST_B)
PCIE1_RX_N: J10.41, U1.54 (PCIE1_RX_N)
PCIE1_RX_P: J10.43, U1.52 (PCIE1_RX_P)
PCIE1_TX_N: J10.47, U1.48 (PCIE1_TX_N)
PCIE1_TX_P: J10.49, U1.46 (PCIE1_TX_P)
PCIE2_CLK_N: U1.66 (PCIE2_REFCLK_N)
PCIE2_CLK_P: U1.64 (PCIE2_REFCLK_P)
PCIE2_RESETn: U1.24 (WIFI_RESET)
PCIE2_RX_N: U1.78 (PCIE2_RX_N)
PCIE2_RX_P: U1.76 (PCIE2_RX_P)
PCIE2_TX_N: U1.72 (PCIE2_TX_N)
PCIE2_TX_P: U1.70 (PCIE2_TX_P)
PCIE_PWR_EN_L: R159.2, U29.4 (EN), U39.13 (IO6)
PHONE_CLK: J12.20, U24.1 (A1)
PHONE_CLK_3V3: R74.1, R86.1, R88.1, U24.20 (B1)
PHONE_DIN: J12.22, U24.3 (A2)
PHONE_DIN_3V3: U1.196 (SAI3_TXD), U24.18 (B2)
PHONE_DOUT: J12.24, U24.4 (A3)
PHONE_DOUT_3V3: U1.194 (SAI3_RXD), U24.17 (B3)
PHONE_DPR: J12.25, U24.8 (A7)
PHONE_DPR_3V3: U8.39 (GPIO27_ADC1), U24.13 (B7)
PHONE_SYNC: J12.28, U24.5 (A4)
PHONE_SYNC_3V3: R21.1, R55.1, U24.16 (B4)
PROG: R36.1, SW1.1
QSPI_CS: R36.2, R38.2, U8.56 (QSPI_SS), U10.1 (~CS)
QSPI_SCK: U8.52 (QSPI_SCLK), U10.6 (CLK)
QSPI_SD0: U8.53 (QSPI_SD0), U10.5 (DI(IO0))
QSPI_SD1: U8.55 (QSPI_SD1), U10.2 (DO(IO1))
QSPI_SD2: U8.54 (QSPI_SD2), U10.3 (IO2)
QSPI_SD3: U8.51 (QSPI_SD3), U10.7 (IO3)
RESET: R56.2, SW2.1 (A), U8.26 (RUN)
RP_FLIGHTMODE: R65.2, R66.2, U8.5 (GPIO3)
RP_FUSB_INT: U8.17 (GPIO14), U23.5 (INT_N)
RP_SCL0: D2.4 (K), J1.7, J20.4, R57.1, U8.3 (GPIO1), U23.6 (SCL), U33.1 (SCL), U34.6 (SCL), U35.36 (CONF1/SCL), U39.1 (SCL)
RP_SDA0: D2.3 (K), J1.6, J20.3, R59.1, U8.2 (GPIO0), U23.7 (SDA), U33.3 (SDA), U34.7 (SDA), U35.38 (CONF2/SDA), U39.2 (SDA)
RP_UART1_RX: J5.3, U8.7 (GPIO5)
RP_UART1_TX: J5.2, U8.6 (GPIO4)
RP_UART2_RX: R12.1, U8.16 (GPIO13)
RP_UART2_TX: R13.2, U8.15 (GPIO12)
SDC_CMD: J2.3 (CMD), U13.20 (B1)
SDC_D0: J2.7 (DAT0), U13.15 (B5)
SDC_D1: J2.8 (DAT1), U13.16 (B4)
SDC_D2: J2.1 (DAT2), U13.17 (B3)
SDC_D3: J2.2 (DAT3/CD), U13.18 (B2)
SD_CLK: U1.22 (SD2_CLK), U14.3 (A)
SD_CMD: U1.20 (SD2_CMD), U13.1 (A1)
SD_D0: U1.12 (SD2_DATA0), U13.6 (A5)
SD_D1: U1.14 (SD2_DATA1), U13.5 (A4)
SD_D2: U1.16 (SD2_DATA2), U13.4 (A3)
SD_D3: U1.18 (SD2_DATA3), U13.3 (A2)
SD_DET: J2.SWB (DET_B), R87.2, U1.26 (SD2_CD)
STANDBY_3V3: C13.2, C25.1, C27.1, C30.1, C31.1, C32.1, C33.1, C34.1, C35.1, C36.1, C40.1, C46.2, C130.1, C131.1, C132.2, C135.1, C142.1, C143.1, C144.1, C148.1, C154.2, C155.2, C156.2, J1.5, J5.1, J20.2, L1.2, R19.2, R38.1, R44.1, R56.1, R57.2, R59.2, R111.2, R113.1, R114.1, R117.2, R127.2, R131.2, R132.1, R133.1, R137.1, TP1.1 (1_1), U2.10 (VCC), U8.1 (IOVDD), U8.10 (IOVDD), U8.22 (IOVDD), U8.33 (IOVDD), U8.42 (IOVDD), U8.43 (ADC_AVDD), U8.44 (VREG_IN), U8.48 (USB_VDD), U8.49 (IOVDD), U10.8 (VCC), U11.8 (VDD), U23.3 (VDD), U23.4 (VDD), U30.10 (VCC), U31.10 (VCC), U33.4 (VCC), U34.8 (VDD), U35.4 (VCC), U35.7 (VCC), U35.10 (VCC), U35.23 (VCC), U35.26 (VCC), U35.29 (VCC), U35.32 (VCC), U39.16 (VDD), U42.3 (FB)
SWC: TP2.1 (1_1), U8.24 (SWCLK)
SWD: TP4.1 (1_1), U8.25 (SWD)
SYS_VCC: C2.1, C5.1, C7.1, C8.1, C11.1, C12.1, C129.1, D5.1 (K), R72.1, R119.2, TP18.1 (1_1), U5.6 (OUT), U6.2 (VIN2), U6.14 (VIN1), U32.6 (IN), U42.5 (VIN)
UART_U+: U37.3 (D2+), U38.14 (USBDP)
UART_U-: U37.7 (D2-), U38.15 (USBDM)
UIM_CLK: J8.3 (CLK), J12.32
UIM_IO: J8.7 (I/O), J12.34
UIM_PWR: J8.1 (VCC), J12.36
UIM_RST: J8.2 (RST), J12.30
UIM_VPP: J8.6 (VPP)
USB1_DN: U1.100 (USB1_D_N), U25.54 (USB_DM_UP)
USB1_DP: U1.102 (USB1_D_P), U25.53 (USB_DP_UP)
USB1_RXN: C128.1, U1.112 (USB1_RX_N)
USB1_RXP: C127.1, U1.114 (USB1_RX_P)
USB1_TXN: U1.106 (USB1_TX_N), U25.59 (USB_SSRXM_UP)
USB1_TXP: U1.108 (USB1_TX_P), U25.58 (USB_SSRXP_UP)
USB2_DN: U1.125 (USB2_D_N), U2.8 (D1-), U30.8 (D1-)
USB2_DP: U1.127 (USB2_D_P), U2.2 (D1+), U30.2 (D1+)
USB2_RXN: U1.121 (USB2_RX_N)
USB2_RXP: U1.119 (USB2_RX_P)
USB2_TXN: U1.115 (USB2_TX_N)
USB2_TXP: U1.113 (USB2_TX_P)
USBH_1A_RXN: J3.B10 (RX1-), U20.1 (IO1), U20.10 (IO1), U25.7 (USB_SSRXM_DN1)
USBH_1A_RXP: J3.B11 (RX1+), U20.2 (IO2), U20.9 (IO2), U25.6 (USB_SSRXP_DN1)
USBH_1A_TXN: C85.2, U25.4 (USB_SSTXM_DN1)
USBH_1A_TXP: C88.2, U25.3 (USB_SSTXP_DN1)
USBH_1B_RXN: J3.A10 (RX2-), U22.4 (IO3), U22.7 (IO3), U25.22 (USB_SSRXP_DN3)
USBH_1B_RXP: J3.A11 (RX2+), U22.5 (IO4), U22.6 (IO4), U25.23 (USB_SSRXM_DN3)
USBH_1B_TXN: C86.2, U25.19 (USB_SSTXP_DN3)
USBH_1B_TXP: C89.2, U25.20 (USB_SSTXM_DN3)
USBH_1V1: C1.1, C3.1, C70.1, C71.1, C74.1, C79.1, C81.1, C100.1, C101.1, R50.2, U25.5 (VDD), U25.8 (VDD), U25.13 (VDD), U25.21 (VDD), U25.28 (VDD), U25.31 (VDD), U25.51 (VDD), U25.57 (VDD)
USBH_1_DN: U25.2 (USB_DM_DN1), U31.8 (D1-)
USBH_1_DP: U25.1 (USB_DP_DN1), U31.2 (D1+)
USBH_2A_RXN: U25.15 (USB_SSRXM_DN2), U35.16 (SSRX+)
USBH_2A_RXP: U25.14 (USB_SSRXP_DN2), U35.17 (SSRX-)
USBH_2A_TXN: U25.12 (USB_SSTXM_DN2), U35.12 (SSTX-)
USBH_2A_TXP: U25.11 (USB_SSTXP_DN2), U35.11 (SSTX+)
USBH_2_DN: U25.10 (USB_DM_DN2), U37.8 (D1-)
USBH_2_DP: U25.9 (USB_DP_DN2), U37.2 (D1+)
USBH_3V3: C6.1, C38.1, C75.1, C80.1, C84.1, C94.1, R25.2, R27.1, U25.16 (VDD33), U25.34 (VDD33), U25.52 (VDD33), U25.63 (VDD33), U40.1 (OUT)
USBH_3_DN: J6.2, U25.18 (USB_DM_DN3)
USBH_3_DP: J6.3, U25.17 (USB_DP_DN3)
USBH_4_DN: J12.9, U25.25 (USB_DM_DN4)
USBH_4_DP: J12.7, U25.24 (USB_DP_DN4)
USBM_DP0_N: R148.2, U35.39 (DP0+)
USBM_DP0_P: R149.2, U35.40 (DP0-)
USBM_DP1_N: R151.2, U35.2 (DP1+)
USBM_DP1_P: R152.2, U35.3 (DP1-)
USBM_DP2_N: R169.2, U35.5 (DP2+)
USBM_DP2_P: R170.2, U35.6 (DP2-)
USBM_DP3_N: R167.2, U35.8 (DP3+)
USBM_DP3_P: R168.2, U35.9 (DP3-)
USBM_DP_AUX_N: C138.1, R157.2, U35.20 (AUX-)
USBM_DP_AUX_P: C137.1, R150.1, U35.19 (AUX+)
USB_LOADER_SW: R116.2, U8.38 (GPIO26_ADC0)
USB_P1_DN: J14.A7 (D-), J14.B7 (D-), U15.4 (IO3), U15.7 (IO3), U37.6 (D-)
USB_P1_DP: J14.A6 (D+), J14.B6 (D+), U15.5 (IO4), U15.6 (IO4), U37.4 (D+)
USB_P2_DN: J3.A7 (D-), J3.B7 (D-), U16.4 (IO3), U16.7 (IO3), U31.6 (D-)
USB_P2_DP: J3.A6 (D+), J3.B6 (D+), U16.5 (IO4), U16.6 (IO4), U31.4 (D+)
USB_SRC1_EN: R143.2, U8.40 (GPIO28_ADC2), U41.4 (EN)
USB_SRC2_EN: R49.2, U8.41 (GPIO29_ADC3), U12.4 (EN)
USB_VBUS: C157.1, C158.1, J14.A4 (VBUS), J14.A9 (VBUS), J14.B4 (VBUS), J14.B9 (VBUS), R31.2, TP16.1 (1_1), U23.2 (VBUS), U27.4 (IN), U27.5 (IN), U27.6 (IN), U41.1 (OUT)
USB_VBUS2: C152.1, C153.1, J3.A4 (VBUS), J3.A9 (VBUS), J3.B4 (VBUS), J3.B9 (VBUS), R83.2, R84.2, TP17.1 (1_1), U12.1 (OUT)
USWITCH_1: R117.1, R122.2, U31.1 (S)
USWITCH_2: R114.2, R123.2, U2.1 (S)
USWITCH_3: R113.2, R124.2, U30.1 (S)
USWITCH_4: R118.2, R131.1, U37.1 (S)
USWITCH_OFF: R141.1, R155.1, U2.9 (~OE), U30.9 (~OE), U31.9 (~OE), U37.9 (~OE)
VCHG: D5.2 (A), J1.3, J1.4, R31.1
WOWWAN: J12.23, R28.2, U24.7 (A6)
WOWWAN_3V3: U8.8 (GPIO6), U24.14 (B6)
~DISP_RESET_1V8: J13.8, R73.1, U7.4
~DISP_RESET_L: R20.1, U7.2, U39.11 (IO4)
~DISP_RESET: U8.4 (GPIO2)
~STANDBY_SHDN: J17.2, R72.2, U42.4 (~SHDN)
~USBH_RESET: R5.2, R69.1, U1.131 (USB_HUB_RESET)

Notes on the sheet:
MAX 28V
open drain
Power Rails
RP2040 has 3.3V IO
3V3
DP0
NOT 1-2199230-5!
Rff
default must be for flashing the rp2040 from the outside. rp2040 can then switch this to other functions.
- Display V1: Backlight is digitally controlled - Display V2: Backlight is PWMed by RP2040 on DISP_EN_L pin
TSOT-23-6
Rfbt
To headphone PCB
DP1
close to VREG_OUT
3v3 I2C Mode
MCLK+BCLK are the same for the modem (CLK). all clocks can be bidrectional.
1V8 -> 3V3
PERp1
MAX 36V
PETp1
place near RP2040
GPIO bank controlled via I2C by System Controller
N/P swapped
PERp3
TODO: AC?
SSD M.2 Card Slot
ILIM (A) = 6800/RLIM (Ω)
Realtime Clock
BRINGUP: confirm these new tx caps
1Gb Ethernet
MIPI-DSI / Display Connector
DisplayPort Alt-Mode Mux
on display v2: HiZ on display v1: low to turn off display
has 10k pulldown (active low)
New in V1.5
Cff
WARNING: do not use B version by accident (active low)
LATER: pci2 unconnected
SWD Debug

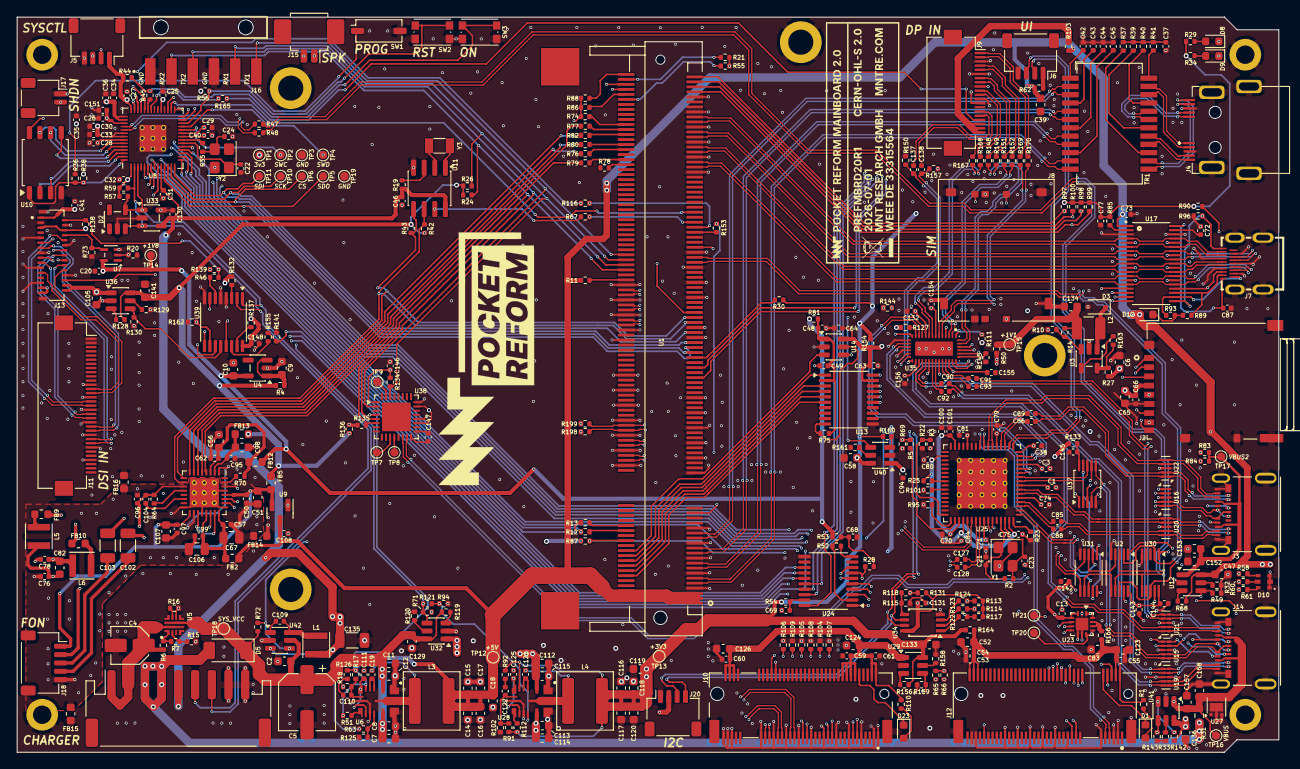
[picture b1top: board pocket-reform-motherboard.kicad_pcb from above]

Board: 6 copper layers, 151.0 x 88.0 mm, 443 parts (0 on the bottom side), 392 nets.

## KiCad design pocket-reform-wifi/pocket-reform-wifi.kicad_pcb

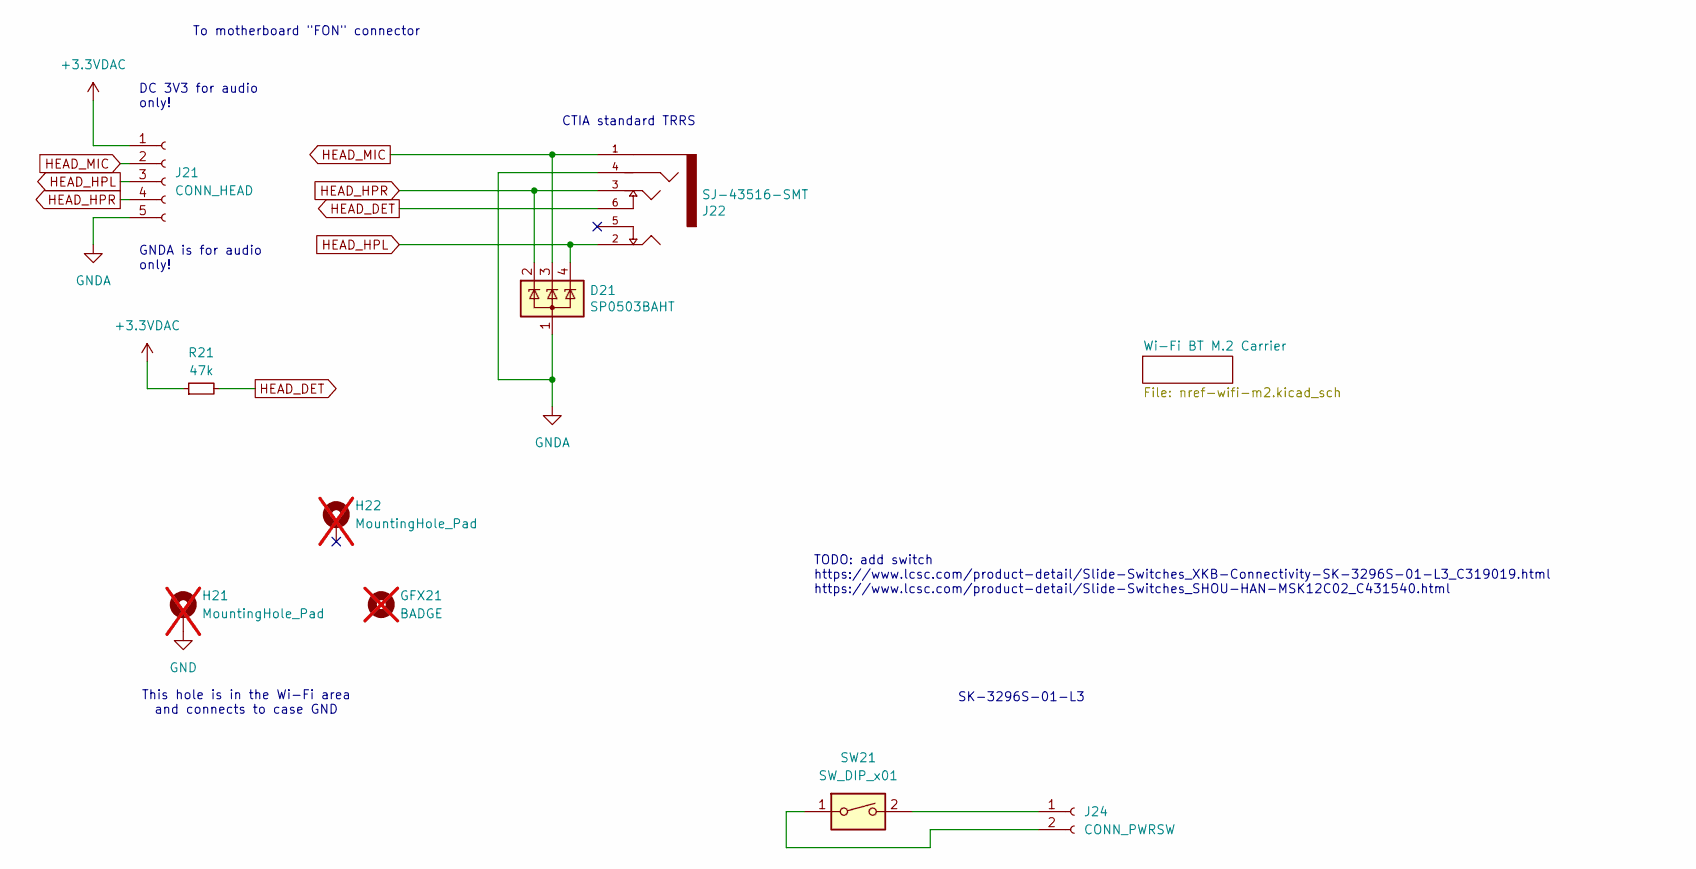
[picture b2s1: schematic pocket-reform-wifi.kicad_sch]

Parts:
D21: SP0503BAHT; SOT-143; LCSC C3040626
GFX21: BADGE; pref-headset-badge; not fitted
H21, H22: MountingHole_Pad; MountingHole_2.2mm_M2_DIN965_Pad; not fitted
J21: CONN_HEAD; JST_SH_SM05B-SRSS-TB_1x05-1MP_P1.00mm_Horizontal; LCSC C136657
J22: SJ-43516-SMT; LCSC global sourcing
J24: CONN_PWRSW; JST_SH_SM02B-SRSS-TB_1x02-1MP_P1.00mm_Horizontal; LCSC C160402
R21: 47k; R_0603_1608Metric; LCSC C105579
SW21: SW_DIP_x01; SW_SPDT_PCM12; LCSC C319019

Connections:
+3.3VDAC: J21.1, R21.1
GND: H21.1; also elsewhere on the board
GNDA: D21.1 (A), J21.5, J22.4 (RING2)
HEAD_DET: J22.6 (RING_SWITCH), R21.2
HEAD_HPL: D21.4 (K), J21.3, J22.2 (TIP)
HEAD_HPR: D21.2 (K), J21.4, J22.3 (RING1)
HEAD_MIC: D21.3 (K), J21.2, J22.1 (SLEEVE)
unnamed: J24.1, SW21.2
unnamed: J24.2, SW21.1

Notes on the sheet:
SK-3296S-01-L3
To motherboard "FON" connector
TODO: add switch https://www.lcsc.com/product-detail/Slide-Switches_XKB-Connectivity-SK-3296S-01-L3_C319019.html https://www.lcsc.com/product-detail/Slide-Switches_SHOU-HAN-MSK12C02_C431540.html
This hole is in the Wi-Fi area and connects to case GND
GNDA is for audio only!
DC 3V3 for audio only!
CTIA standard TRRS

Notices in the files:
pocket-reform-motherboard/pocket-reform-motherboard.kicad_sch:
License: OHL-S 2.0
